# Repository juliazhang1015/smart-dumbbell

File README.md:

# Smart Dumbbell

A lightweight dumbbell that counts bicep curls on the device, reads heart rate at the grip, and lets a connected laptop view the session live and export it as CSV. Built for CCCARE participants who do prescribed curls at home on their own: no smartwatch, phone app or cloud account needed.

ECE 198 design project, Group 57, University of Waterloo, Fall 2026.

*Concept render.*

## Features

- **Counts curls on the device.** A swing-angle rule is combined with a motion classifier running on the microcontroller, which reduces false counts from other movement such as shaking, raises and putting the dumbbell down.
- **Heart rate at the grip.** An optical sensor under the finger; the display shows `--` instead of a stale value when the reading is not valid.
- **Feedback on the dumbbell.** OLED with session state, reps, BPM and the current movement label; an LED while a set is running and a beep on each counted rep.
- **One-button control.** Short press to start, pause or resume; hold to end the set.
- **Live view and export.** The dumbbell hosts its own Wi-Fi network with a live page, and sends a Bluetooth packet every 250 ms to a dashboard on a laptop. Once connected, the session can be watched in real time and exported as CSV.
- **Self-contained.** Counting and the display keep working when no computer is connected.

## Hardware

| Part | Component |
|---|---|
| Controller | Arduino Nano ESP32 (ESP32-S3) |
| Motion | Adafruit LSM6DSOX accelerometer and gyroscope, 104 Hz |
| Heart rate | MAX30102 optical pulse sensor, 100 Hz |
| Display | SSD1306 OLED, 128×64 |
| Controls and feedback | One push button, LED, buzzer |
| Power | 5000 mAh USB-C power bank |
| Enclosure | 3D-printed hollow shell holding the power bank, a soldered perfboard hub and the sensors |

All three modules share one I2C bus at 400 kHz. See the [wiring and schematic](hardware/wiring/README.md), the [enclosure CAD](hardware/cad/) and the [parts list](docs/hardware.md).

## How it works

```text
Offline:  recordings -> labels -> training -> C header

LSM6DSOX (accel + gyro, 104 Hz) -> 2 s buffer -> angle rule finds a candidate rep
                                              -> model on the last 2 s: curl? -> count + beep
MAX30102 (100 Hz) -> contact check -> plausible beat intervals -> mean of 4 beats, or "--"
                                              |
                               OLED, LED, buzzer on the device
                                              |
                 Wi-Fi access point (live page, CSV)  ·  Bluetooth packet every 250 ms
```

The motion model is a logistic regression on 31 features of a 2 s window, with three classes (`curl`, `idle`, `other`) and 96 weights. Forty labelled recordings were collected from five participants; the final model is trained on a laptop from 35 of them and exported as a C header, so the Nano runs it in plain C++ without an ML runtime. A rep is counted when the swing is at least 60° and back and the model labels the 2 s ending at that rep as `curl`. Details are in the [model card](ml/model-card.md).

## Performance

| Measure | Result |
|---|---|
| Classification, leave-one-participant-out over five participants | Macro-F1 0.872 |
| Inference time on the Nano ESP32 | About 2.2 ms per window |
| Counting, firmware rule replayed on the recordings | 217 of 223 complete curls counted |
| False reps during other movement, same replay | 26 without the model check, 1 with it |
| Counting on the board, one person holding the bare board | 23 of 25 complete curls counted; the two missed were curls where the hand hit a laptop. 0 false reps during other movement |

Test records are in [tests/results](tests/results/).

## Getting started

Build and upload the firmware with `arduino-cli`:

```bash
arduino-cli compile --fqbn arduino:esp32:nano_nora firmware/SmartDumbbell
arduino-cli upload  --fqbn arduino:esp32:nano_nora -p /dev/cu.usbmodem<id> firmware/SmartDumbbell
```

Required libraries, pin assignments and the serial, Wi-Fi and Bluetooth output formats are in the [firmware README](firmware/SmartDumbbell/README.md).

To view a session on a Mac, run the [live dashboard](software/live-dashboard/README.md). It receives the Bluetooth packets and shows reps, cadence, heart rate and movement labels, with short AI feedback on the current set. Without a dashboard, join the dumbbell's Wi-Fi network and open `http://192.168.4.1/` for the live page and CSV download. Open the page before starting a set: the CSV holds only the rows received while the page is open.

To retrain the model from the recordings, see [ml/README.md](ml/README.md).

## Repository structure

| Directory | Contents |
|---|---|
| `firmware/` | `SmartDumbbell/` is the main sketch; `classifier/` holds the model code and weights, `bringup/` the single-module test sketches, `app/` and `demo/` earlier sketches |
| `ml/` | Recording protocol, training and export pipeline, offline replay tools, model card |
| `data/` | Labelled IMU recordings |
| `software/` | Live dashboard, an earlier Web Bluetooth page (for the older 16-byte packet), Python logger |
| `hardware/` | Enclosure CAD, wiring diagrams, schematic, perfboard hub drawings, renders |
| `docs/` | [Specification](docs/specification.md), [decision log](docs/decisions.md), hardware and budget, background research |
| `tests/` | Dated test records |
| `presentation/` | Pitch and progress-update decks |

## Team

| Member | Main work |
|---|---|
| [Hanson He](https://github.com/HansonHe-UW) | Motion classifier (IMU recordings, training pipeline, on-device inference), model-confirmed rep counting in the firmware, board bring-up and testing, perfboard hub layout, macOS live dashboard |
| [Eric Zhu](https://github.com/ericzhu0220) | Enclosure design and 3D printing, fit checks and assembly of the prototype, help with motion data collection and model training |
| [Zoe Wang](https://github.com/ZoeWang0607) | Electronics and wiring, SmartDumbbell firmware with Wi-Fi and Bluetooth, Web Bluetooth dashboard |
| [Julia Zhang](https://github.com/juliazhang1015) | Circuit schematic, first integrated demo firmware, offline rep-counting tools, Python data logger, background research and documentation |

## License

This is a student course project, not an official University of Waterloo or CCCARE product and not a medical device. No open-source license has been selected.

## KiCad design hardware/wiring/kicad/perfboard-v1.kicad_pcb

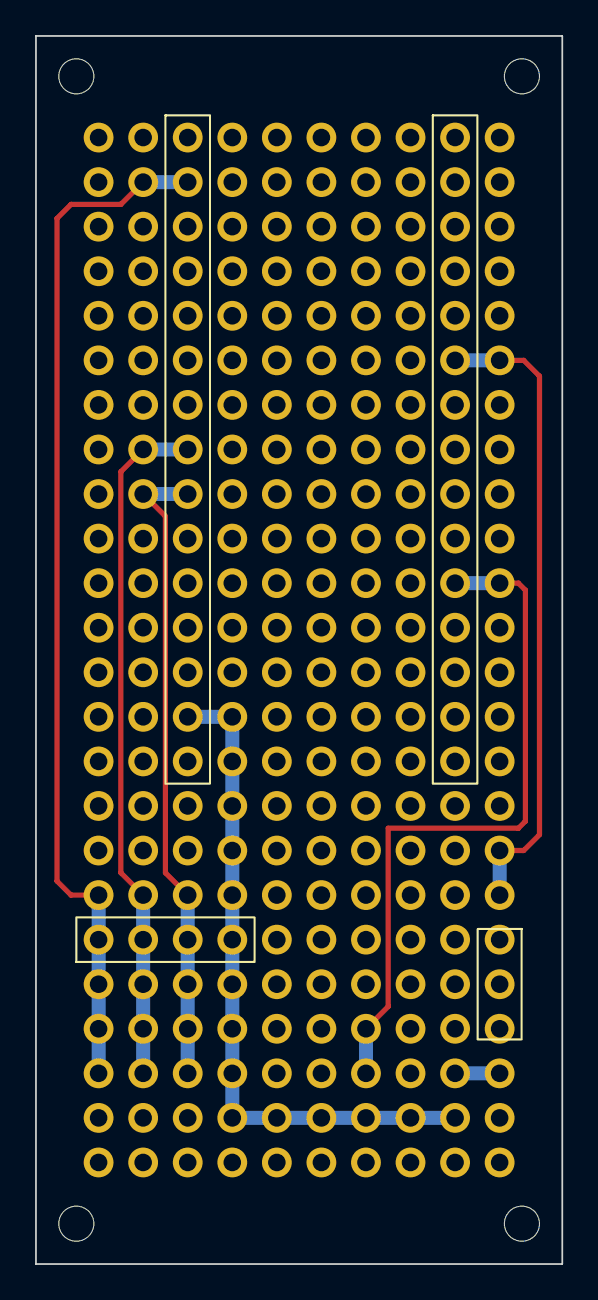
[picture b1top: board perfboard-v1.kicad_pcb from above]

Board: 2 copper layers, 30.0 x 70.0 mm, 5 parts (0 on the bottom side), 7 nets.

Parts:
J1: IMU 4209 cable (1x4); PinSocket_1x04_P2.54mm_Vertical
J10: Nano socket JP1 (1x15); PinSocket_1x15_P2.54mm_Vertical
J11: Nano socket JP2 (1x15); PinSocket_1x15_P2.54mm_Vertical
PB1: Perfboard 30x70, 10x24 holes; Perfboard_30x70_10x24
R1: 220R; R_Axial_DIN0207_L6.3mm_D2.5mm_P10.16mm_Horizontal

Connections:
+3V3: PB1.A18, PB1.A19, PB1.A20, PB1.A21, PB1.A22, PB1.B2, PB1.C2
D2_SW1: PB1.G21, PB1.G22, PB1.I11, PB1.J11
D7_LED: PB1.I6, PB1.J6, PB1.J17, PB1.J18
GND: PB1.C14, PB1.D14, PB1.D15, PB1.D16, PB1.D17, PB1.D18, PB1.D19, PB1.D20, PB1.D21, PB1.D22, PB1.D23, PB1.E23, PB1.F23, PB1.G23, PB1.H23, PB1.I23
LED_A: PB1.I22, PB1.J22
SCL: PB1.B9, PB1.C9, PB1.C18, PB1.C19, PB1.C20, PB1.C21, PB1.C22
SDA: PB1.B8, PB1.B18, PB1.B19, PB1.B20, PB1.B21, PB1.B22, PB1.C8
